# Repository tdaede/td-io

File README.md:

td-io is a JVS I/O board designed to adapt older JAMMA-compatible cabinets to the newer JVS standard, used by modern arcade hardware such as the Naomi and exA. It features a number of independent systems to translate signals, drive cabinet hardware, and power JVS games.

# Features at a glance

* Chainable JVS I/O implementing a 2L12B panel and coin inputs
* JVS to JAMMA video converter compatible with all monitors
* Mono/stereo audio amplifier for driving JAMMA speakers
* JVS power connector providing 3.3V via an on-board converter
* High reliability, low heat generation and all solid state caps
* Upgradeable firmware

# Comparison with other JVS I/O options

|               | TD-IO   | Capcom I/O   | Sega 838   | Exa I/O |
| ------------- | ------- | ------------ | ---------- | ------- |
| Lag (frames)  | 0       | 1            | 0          | 0       |
| Chaining      | ✔ | ❌ | ✔ | ✔ |
| Video         | ✔ | ✔ | ✔ | ❌ |
| Audio amp     | ✔ | ✔ | ❌ | ❌ |
| 3.3V power    | ✔ | ✔ | ❌ | ❌ |
| Amplified stereo | ✔ | ❌ | ❌ | ❌ |

# JVS inputs

The JVS I/O bus connects to the board via USB-style A and B connectors. Daisy chaining is supported. The I/O presents two players, each with a single joystick/lever and six buttons. Joystick and button 1-4 inputs are mapped to the JAMMA edge connector, and buttons 4-6 are mapped to a CPS2-style kick harness connector. Buttons are polled synchronously, ensuring microsecond-level latency.

Service, test, and tilt buttons are also supported. JAMMA's single service button is mapped to JVS player 1's service button.

The board also presents one or two coin slots, toggleable by a DIP switch. The board also features two coin meter drivers and two coin lockout drivers. Coins are locked out when the respective coin count is set to its max value (16383).

# Video

The board maps JVS-level video (0.7Vp-p, AC or DC coupled) to JAMMA levels (0-3V, DC coupled). This is achieved via a DC restore step using the sync signal, followed by a fixed amplification. The DC coupled output allows maximum compatibility with monitors such as the Nanao MS8 and capture devices such as the Splitfire which require it.

In addition, a sync combiner combines negative H/V sync to negative composite sync.

No rate conversion is performed - the monitor must support the same scan rates as the JVS game.

An EDID EEPROM is also attached to the VGA port, to identify as a 31kHz monitor.

# Audio

TD-IO provides a class-D audio amplifier, which can drive both mono and stereo speakers in JAMMA cabinets. For mono cabinets, audio is simply provided via the JAMMA edge. For stereo support, the cabinet's speakers should be connected to the JST NH header provided on the I/O. The pinout of this header is directly compatible with the Egret 2, and adapters can be easily made for other cabinets, such as the Aero.

The stereo/mono switch selects whether to mixdown the L/R channels to mono. It should be set to mono when using a mono cabinet via the JAMMA edge, and stereo when using a cabinet with the stereo header.

The stereo support is not directly compatible with nonstandard Neo Geo style stereo over JAMMA, with a common ground. For these cabinets, either use the TD-IO in mono mode, or rewire the cabinet to connect directly to the stereo header. The left/right negative speaker outputs should not be tied together.

## Aero City stereo adapter

| JST NH H4P-SHF-AA | Molex MLX 50-84-2042 |
| --- | --- |
| 1   | 2   |
| 2   | 3   |
| 3   | 1   |
| 4   | 4   |

# Power

An 8-pin JVS power connector forwards 12V and 5V from the cabinet to the JVS board. In addition, an on-board power supply generates 3.3V at up to 7A from the cabinet's 5V rail for systems that require it, such as Naomi.

The cabinet's 5V power supply must still be adequate to power the 3.3V converter.

The IO's electronics are protected from overvoltage and overcurrent by an automatically resetting protector.

# Firmware Updates

The board features an on-board RP2040 microcontroller, whose firmware can be updated over USB for feature enhancements or compatibility fixes.

To update the firmware, turn off power to the cabinet (if attached). Then, attach a USB cable to the micro USB connector. Hold down the white button on the RP2040 while plugging the USB connector into a PC. The TD-IO will then appear as a flash drive. Copy the firmware file (ending in .uf2) onto the drive. The TD-IO will then disconnect and be ready for use.

# Analog Input

The board features an unpopulated expansion header exposing 3 3.3V level analog inputs, designed for potentiometers for analog joystick or racing games. This feature is experimental and not yet implemented in the firmware.

# Where to buy

The board is not currently for sale, as testing is not yet complete.

# License

CERN-OHL-W

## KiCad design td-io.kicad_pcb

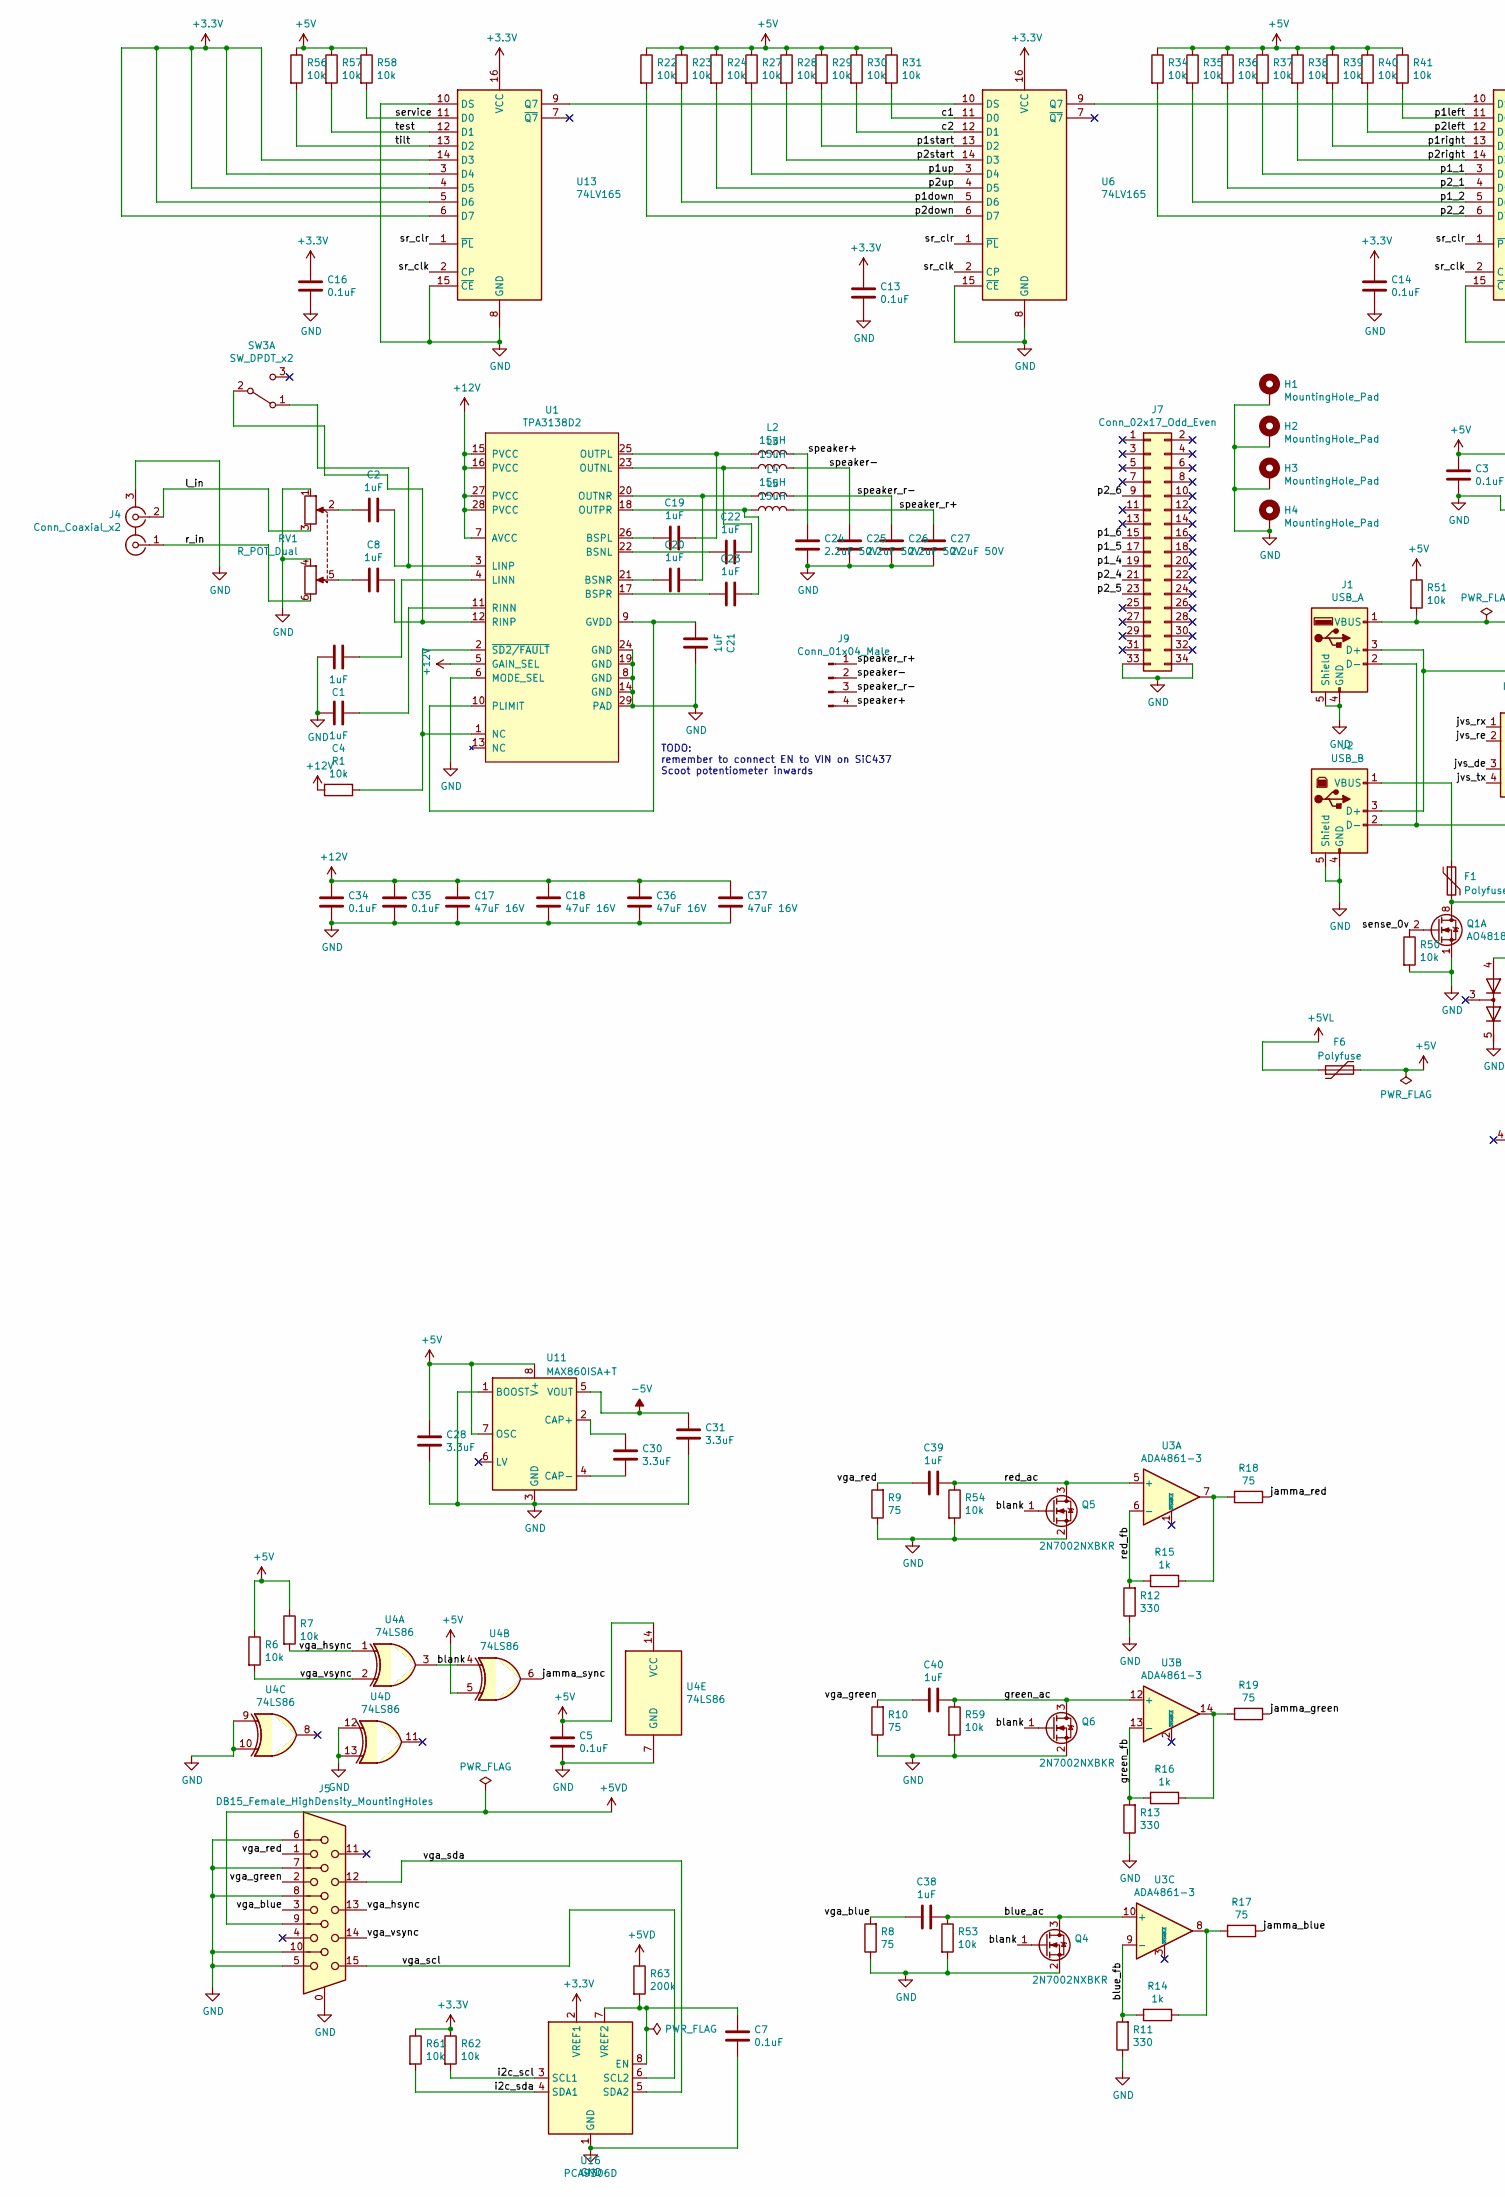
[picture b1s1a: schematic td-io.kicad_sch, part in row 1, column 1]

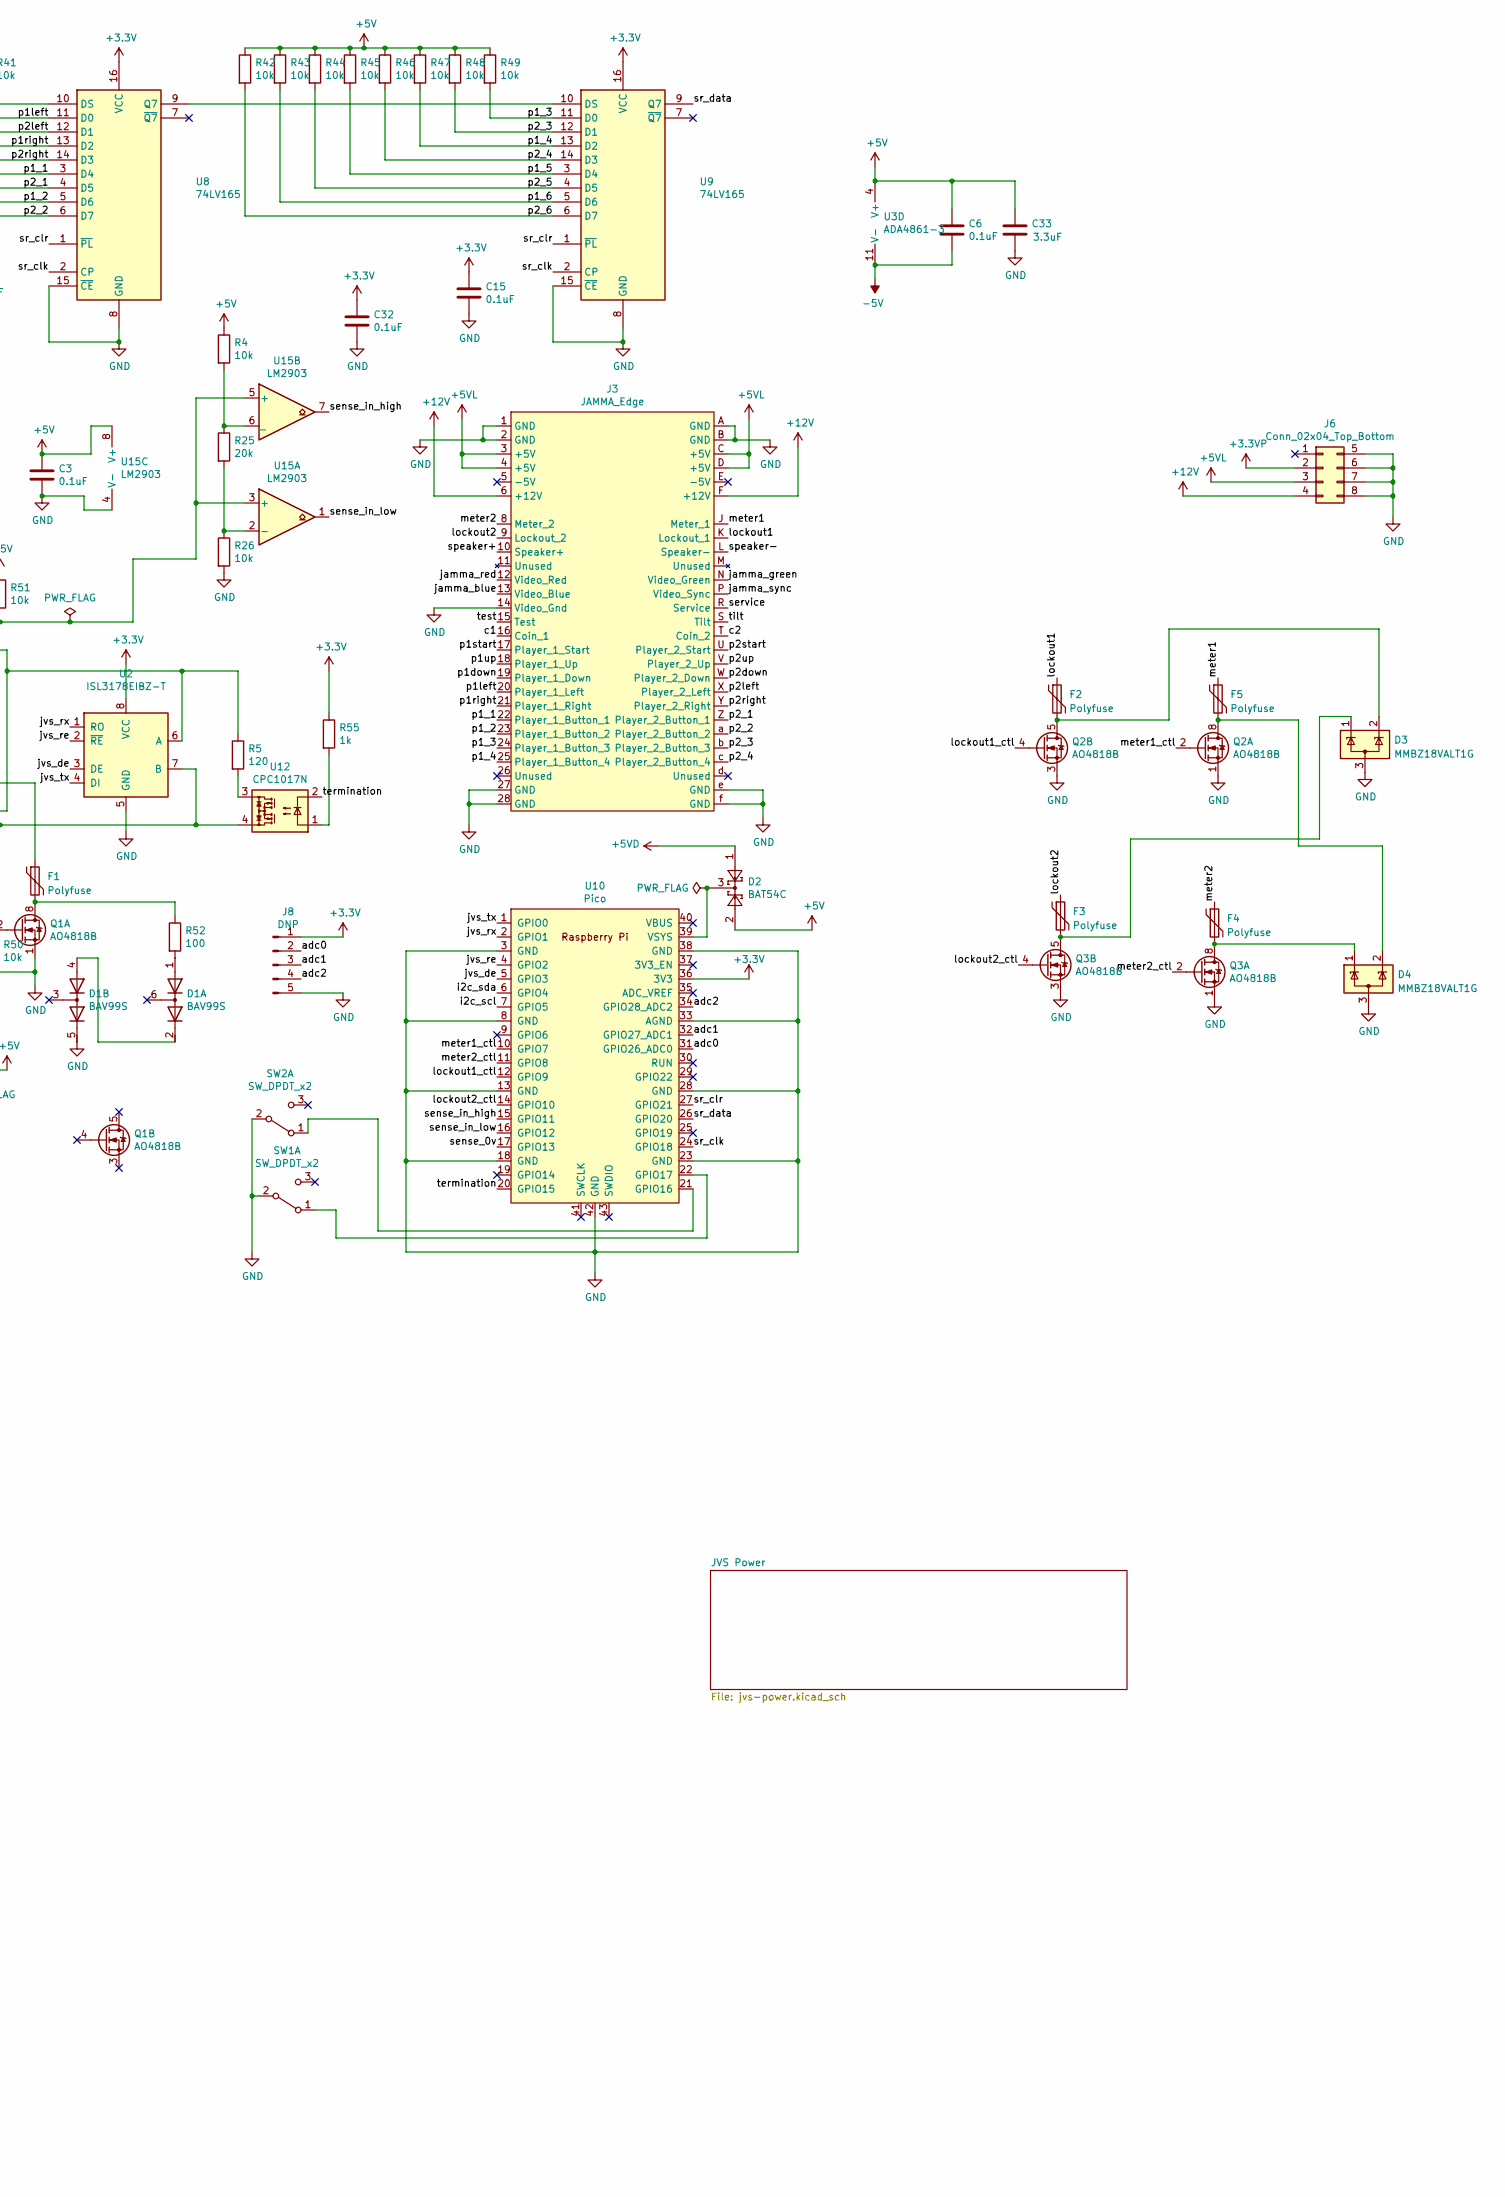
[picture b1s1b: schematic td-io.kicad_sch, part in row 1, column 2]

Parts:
C1, C2, C4, C8, C19, C20, C21, C22, C23, C38, C39, C40: 1uF; C_0805_2012Metric; Digikey 1276-2926-1-ND
C3, C5, C6, C7, C13, C14, C15, C16, C32, C34, C35: 0.1uF; C_0805_2012Metric; Digikey 1276-2444-1-ND
C17, C18, C36, C37: 47uF 16V; C_1210_3225Metric; Digikey 490-16309-1-ND
C24, C25, C26, C27: 2.2uF 50V; C_1210_3225Metric; Digikey 1276-2884-1-ND
C28, C30, C31, C33: 3.3uF; C_0805_2012Metric; Digikey 1276-6461-1-ND
D1: BAV99S; SOT-363_SC-70-6; Digikey 1727-4042-1-ND
D2: BAT54C; SOT-23; Digikey BAT54CFSCT-ND
D3, D4: MMBZ18VALT1G; SOT-23; Digikey MMBZ18VALT1GOSTR-ND
F1, F2, F3, F4, F5, F6: Polyfuse; R_1812_4532Metric; Digikey 507-1762-1-ND
H1, H2, H3, H4: MountingHole_Pad; MountingHole_3.2mm_M3_Pad_Via
J1: USB_A; USB_A_Molex_67643_Horizontal; Digikey SAM10870-ND
J2: USB_B; USB_B_OST_USB-B1HSxx_Horizontal; Digikey SAM10873-ND
J3: JAMMA_Edge; JAMMA
J4: Conn_Coaxial_x2; PJRAN2X1U01AUX; Digikey SC2534-ND
J5: DB15_Female_HighDensity_MountingHoles; DSUB-15-HD_Female_Horizontal_P2.29x2.5mm_EdgePinOffset8.35m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; Digikey Z13226-ND
J6: Conn_02x04_Top_Bottom; B08P-VL; Digikey 455-2365-ND
J7: Conn_02x17_Odd_Even; DF1BZ-34DP-2.5DS; Digikey H11039-ND
J8: DNP; PinHeader_1x05_P2.54mm_Vertical
J9: Conn_01x04_Male; JST_SH_B4B-NH-A_1x04_P2.50mm_Vertical; Digikey 455-4179-ND
L2, L3, L4, L5: 15uH; L_7.3x7.3_H4.5; Digikey 811-3582-1-ND
Q1, Q2, Q3: AO4818B; SOIC-8_3.9x4.9mm_P1.27mm; Digikey 785-1059-1-ND
Q4, Q5, Q6: 2N7002NXBKR; SOT-23; Digikey 1727-8642-1-ND
R1, R4, R6, R7, R22, R23, R24, R26, R27, R28, R29, R30, R31, R34, R35, R36, R37, R38, R39, R40, R41, R42, R43, R44, R45, R46, R47, R48, R49, R50, R51, R53, R54, R56, R57, R58, R59, R61, R62: 10k; R_0805_2012Metric; Digikey 311-10.0KCRCT-ND
R5: 120; R_0805_2012Metric; Digikey 13-RT0805FRE07120RLCT-ND
R8, R9, R10, R17, R18, R19: 75; R_0805_2012Metric; Digikey 311-75.0CRCT-ND
R11, R12, R13: 330; R_0805_2012Metric; Digikey 311-330CRCT-ND
R14, R15, R16, R55: 1k; R_0805_2012Metric; Digikey 311-1.00KCRCT-ND
R25: 20k; R_0805_2012Metric; Digikey 311-20.0KCRCT-ND
R52: 100; R_0805_2012Metric; Digikey 311-100CRCT-ND
R63: 200k; R_0805_2012Metric; Digikey 311-200KCRCT-ND
RV1: R_POT_Dual; PTV112-4420A-A503; Digikey PTV112-4420A-A503-ND
SW1, SW2, SW3: SW_DPDT_x2; SW_DPDT_CK_JS202011JCQN; Digikey CKN10723CT-ND
U1: TPA3138D2; HTSSOP-28-1EP_4.4x9.7mm_P0.65mm_tpa3138_ThermalVias; Digikey 296-50219-ND
U2: ISL3178EIBZ-T; SOIC-8_3.9x4.9mm_P1.27mm; Digikey 20-ISL3178EIBZ-TCT-ND
U3: ADA4861-3; SOIC-14_3.9x8.7mm_P1.27mm; Digikey ADA4861-3YRZ-RL7CT-ND
U4: 74LS86; SOIC-14_3.9x8.7mm_P1.27mm; Digikey 296-8201-1-ND
U6, U8, U9, U13: 74LV165; SOIC-16_3.9x9.9mm_P1.27mm; Digikey 296-SN74LV165ADRG3CT-ND
U10: Pico; RPi_Pico_SMD; Digikey 2648-SC0915CT-ND
U11: MAX860ISA+T; SOIC-8_3.9x4.9mm_P1.27mm; Digikey MAX860ISA+TCT-ND
U12: CPC1017N; SOP-4_3.8x4.1mm_P2.54mm; Digikey CLA153-ND
U15: LM2903; SOIC-8_3.9x4.9mm_P1.27mm; Digikey 296-27463-1-ND
U16: PCA9306D; SO-8_3.9x4.9mm_P1.27mm; Digikey 568-4215-1-ND

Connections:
+3.3V: C13.1, C14.1, C15.1, C16.1, C32.1, J8.1, R55.1, R61.1, R62.1, U2.8 (VCC), U6.16 (VCC), U8.16 (VCC), U9.16 (VCC), U10.36 (3V3), U13.3 (D4), U13.4 (D5), U13.5 (D6), U13.6 (D7), U13.14 (D3), U13.16 (VCC), U16.2 (VREF1)
+3.3VP: J6.2; also elsewhere on the board
+5V: C3.1, C5.1, C6.1, C28.1, C33.1, D2.2, F6.2, R4.1, R6.1, R7.1, R22.1, R23.1, R24.1, R27.1, R28.1, R29.1, R30.1, R31.1, R34.1, R35.1, R36.1, R37.1, R38.1, R39.1, R40.1, R41.1, R42.1, R43.1, R44.1, R45.1, R46.1, R47.1, R48.1, R49.1, R51.1, R56.1, R57.1, R58.1, U3.4 (V+), U4.5, U4.14 (VCC), U11.7 (OSC), U11.8 (V+), U15.8 (V+)
+5VD: D2.1, J5.9, R63.1
+5VL: F6.1, J3.3 (+5V), J3.4 (+5V), J3.C (+5V), J3.D (+5V), J6.3; also elsewhere on the board
+12V: C17.1, C18.1, C34.1, C35.1, C36.1, C37.1, J3.6 (+12V), J3.F (+12V), J6.4, R1.2, U1.5 (GAIN_SEL), U1.7 (AVCC), U1.15 (PVCC), U1.16 (PVCC), U1.27 (PVCC), U1.28 (PVCC)
-5V: C6.2, C31.1, U3.11 (V-), U11.5 (VOUT)
/adc0: J8.2, U10.31 (GPIO26_ADC0)
/adc1: J8.3, U10.32 (GPIO27_ADC1)
/adc2: J8.4, U10.34 (GPIO28_ADC2)
/blank: Q4.1 (G), Q5.1 (G), Q6.1 (G), U4.3, U4.4
/blue_ac: C38.1, Q4.3 (D), R53.1, U3.10 (+)
/blue_fb: R11.2, R14.2, U3.9 (-)
/c1: J3.16 (Coin_1), R31.2, U6.11 (D0)
/c2: J3.T (Coin_2), R30.2, U6.12 (D1)
/green_ac: C40.1, Q6.3 (D), R59.1, U3.12 (+)
/green_fb: R13.2, R16.2, U3.13 (-)
/i2c_scl: R62.2, U10.7 (GPIO5), U16.3 (SCL1)
/i2c_sda: R61.2, U10.6 (GPIO4), U16.4 (SDA1)
/jamma_blue: J3.13 (Video_Blue), R17.1
/jamma_green: J3.N (Video_Green), R19.1
/jamma_red: J3.12 (Video_Red), R18.1
/jamma_sync: J3.P (Video_Sync), U4.6
/jvs_de: U2.3 (DE), U10.5 (GPIO3)
/jvs_re: U2.2 (~RE), U10.4 (GPIO2)
/jvs_rx: U2.1 (RO), U10.2 (GPIO1)
/jvs_tx: U2.4 (DI), U10.1 (GPIO0)
/l_in: J4.2 (IN2), RV1.3
/lockout1: F2.1, J3.K (Lockout_1)
/lockout1_ctl: Q2.4 (G2), U10.12 (GPIO9)
/lockout2: F3.1, J3.9 (Lockout_2)
/lockout2_ctl: Q3.4 (G2), U10.14 (GPIO10)
/meter1: F5.1, J3.J (Meter_1)
/meter1_ctl: Q2.2 (G1), U10.10 (GPIO7)
/meter2: F4.1, J3.8 (Meter_2)
/meter2_ctl: Q3.2 (G1), U10.11 (GPIO8)
/p1_1: J3.22 (Player_1_Button_1), R37.2, U8.3 (D4)
/p1_2: J3.23 (Player_1_Button_2), R35.2, U8.5 (D6)
/p1_3: J3.24 (Player_1_Button_3), R49.2, U9.11 (D0)
/p1_4: J3.25 (Player_1_Button_4), J7.19, R47.2, U9.13 (D2)
/p1_5: J7.17, R45.2, U9.3 (D4)
/p1_6: J7.15, R43.2, U9.5 (D6)
/p1down: J3.19 (Player_1_Down), R23.2, U6.5 (D6)
/p1left: J3.20 (Player_1_Left), R41.2, U8.11 (D0)
/p1right: J3.21 (Player_1_Right), R39.2, U8.13 (D2)
/p1start: J3.17 (Player_1_Start), R29.2, U6.13 (D2)
/p1up: J3.18 (Player_1_Up), R27.2, U6.3 (D4)
/p2_1: J3.Z (Player_2_Button_1), R36.2, U8.4 (D5)
/p2_2: J3.a (Player_2_Button_2), R34.2, U8.6 (D7)
/p2_3: J3.b (Player_2_Button_3), R48.2, U9.12 (D1)
/p2_4: J3.c (Player_2_Button_4), J7.21, R46.2, U9.14 (D3)
/p2_5: J7.23, R44.2, U9.4 (D5)
/p2_6: J7.9, R42.2, U9.6 (D7)
/p2down: J3.W (Player_2_Down), R22.2, U6.6 (D7)
/p2left: J3.X (Player_2_Left), R40.2, U8.12 (D1)
/p2right: J3.Y (Player_2_Right), R38.2, U8.14 (D3)
/p2start: J3.U (Player_2_Start), R28.2, U6.14 (D3)
/p2up: J3.V (Player_2_Up), R24.2, U6.4 (D5)
/r_in: J4.1 (IN1), RV1.6
/red_ac: C39.1, Q5.3 (D), R54.1, U3.5 (+)
/red_fb: R12.2, R15.2, U3.6 (-)
/sense_0v: Q1.2 (G1), R50.1, U10.17 (GPIO13)
/sense_in_high: U10.15 (GPIO11), U15.7
/sense_in_low: U10.16 (GPIO12), U15.1
/service: J3.R (Service), R58.2, U13.11 (D0)
/speaker+: C24.1, J3.10 (Speaker+), J9.4, L2.2
/speaker-: C25.1, J3.L (Speaker-), J9.2, L3.2
/speaker_r+: C27.1, J9.1, L5.2
/speaker_r-: C26.1, J9.3, L4.2
/sr_clk: U6.2 (CP), U8.2 (CP), U9.2 (CP), U10.24 (GPIO18), U13.2 (CP)
/sr_clr: U6.1 (~PL), U8.1 (~PL), U9.1 (~PL), U10.27 (GPIO21), U13.1 (~PL)
/sr_data: U9.9 (Q7), U10.26 (GPIO20)
/termination: U10.20 (GPIO15), U12.2
/test: J3.15 (Test), R57.2, U13.12 (D1)
/tilt: J3.S (Tilt), R56.2, U13.13 (D2)
/vga_blue: C38.2, J5.3, R8.2
/vga_green: C40.2, J5.2, R10.2
/vga_hsync: J5.13, R7.2, U4.1
/vga_red: C39.2, J5.1, R9.2
/vga_scl: J5.15, U16.6 (SCL2)
/vga_sda: J5.12, U16.5 (SDA2)
/vga_vsync: J5.14, R6.2, U4.2
GND: C1.1, C3.2, C4.1, C5.2, C7.2, C13.2, C14.2, C15.2, C16.2, C17.2, C18.2, C21.1, C24.2, C25.2, C26.2, C27.2, C28.2, C31.2, C32.2, C33.2, C34.2, C35.2, C36.2, C37.2, D1.5 (K4), D3.3 (A), D4.3 (A), H1.1, H2.1, H3.1, H4.1, J1.4 (GND), J1.5 (Shield), J2.4 (GND), J2.5 (Shield), J3.1 (GND), J3.2 (GND), J3.14 (Video_Gnd), J3.27 (GND), J3.28 (GND), J3.A (GND), J3.B (GND), J3.e (GND), J3.f (GND), J4.3 (EXT), J5.0, J5.5, J5.6, J5.7, J5.8, J5.10, J6.5, J6.6, J6.7, J6.8, J7.33, J7.34, J8.5, Q1.1 (S1), Q2.1 (S1), Q2.3 (S2), Q3.1 (S1), Q3.3 (S2), Q4.2 (S), Q5.2 (S), Q6.2 (S), R8.1, R9.1, R10.1, R11.1, R12.1, R13.1, R26.2, R50.2, R53.2, R54.2, R59.2, RV1.1, RV1.4, SW1.2 (B), SW2.2 (B), U1.6 (MODE_SEL), U1.8 (GND), U1.14 (GND), U1.19 (GND), U1.24 (GND), U1.29 (PAD), U2.5 (GND), U4.7 (GND), U4.9, U4.10, U4.12, U4.13, U6.8 (GND), U6.15 (~CE), U8.8 (GND), U8.15 (~CE), U9.8 (GND), U9.15 (~CE), U10.3 (GND), U10.8 (GND), U10.13 (GND), U10.18 (GND), U10.23 (GND), U10.28 (GND), U10.33 (AGND), U10.38 (GND), U10.42 (GND), U11.1 (BOOST), U11.3 (GND), U13.8 (GND), U13.10 (DS), U13.15 (~CE), U15.4 (V-), U16.1 (GND); also elsewhere on the board
unnamed: C1.2, U1.4 (LINN)
unnamed: C2.1, SW3.1 (A), U1.3 (LINP)
unnamed: C2.2, RV1.2
unnamed: C4.2, U1.11 (RINN)
unnamed: C7.1, R63.2, U16.7 (VREF2), U16.8 (EN)
unnamed: C8.1, SW3.2 (B), U1.12 (RINP)
unnamed: C8.2, RV1.5
unnamed: C19.1, L2.1, U1.25 (OUTPL)
unnamed: C19.2, U1.26 (BSPL)
unnamed: C20.1, L4.1, U1.20 (OUTNR)
unnamed: C20.2, U1.21 (BSNR)
unnamed: C21.2, U1.9 (GVDD), U1.10 (PLIMIT)
unnamed: C22.1, L3.1, U1.23 (OUTNL)
unnamed: C22.2, U1.22 (BSNL)
unnamed: C23.1, L5.1, U1.18 (OUTPR)
unnamed: C23.2, U1.17 (BSPR)
unnamed: C30.1, U11.2 (CAP+)
unnamed: C30.2, U11.4 (CAP-)
unnamed: D1.1 (A1), R52.2
unnamed: D1.2 (K2), D1.4 (A3)
unnamed: D2.3, U10.39 (VSYS)
unnamed: D3.1 (K), F3.2, Q3.5 (D2), Q3.6 (D2)
unnamed: D3.2 (K), F2.2, Q2.5 (D2), Q2.6 (D2)
unnamed: D4.1 (K), F4.2, Q3.7 (D1), Q3.8 (D1)
unnamed: D4.2 (K), F5.2, Q2.7 (D1), Q2.8 (D1)
unnamed: F1.1, J2.1 (VBUS)
unnamed: F1.2, Q1.7 (D1), Q1.8 (D1), R52.1
unnamed: J1.1 (VBUS), R51.2, U15.3 (+), U15.5 (+)
unnamed: J1.2 (D-), J2.2 (D-), U2.7 (B), U12.4
unnamed: J1.3 (D+), J2.3 (D+), R5.1, U2.6 (A)
unnamed: R1.1, U1.1 (NC), U1.2 (~SD2/FAULT)
unnamed: R5.2, U12.3
unnamed: R14.1, R17.2, U3.8
unnamed: R15.1, R18.2, U3.7
unnamed: R16.1, R19.2, U3.14
unnamed: R4.2, R25.1, U15.6 (_)
unnamed: R25.2, R26.1, U15.2 (-)
unnamed: R55.2, U12.1
unnamed: SW1.1 (A), U10.22 (GPIO17)
unnamed: SW2.1 (A), U10.21 (GPIO16)
unnamed: U6.9 (Q7), U8.10 (DS)
unnamed: U8.9 (Q7), U9.10 (DS)
unnamed: U6.10 (DS), U13.9 (Q7)

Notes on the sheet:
TODO: remember to connect EN to VIN on SiC437 Scoot potentiometer inwards

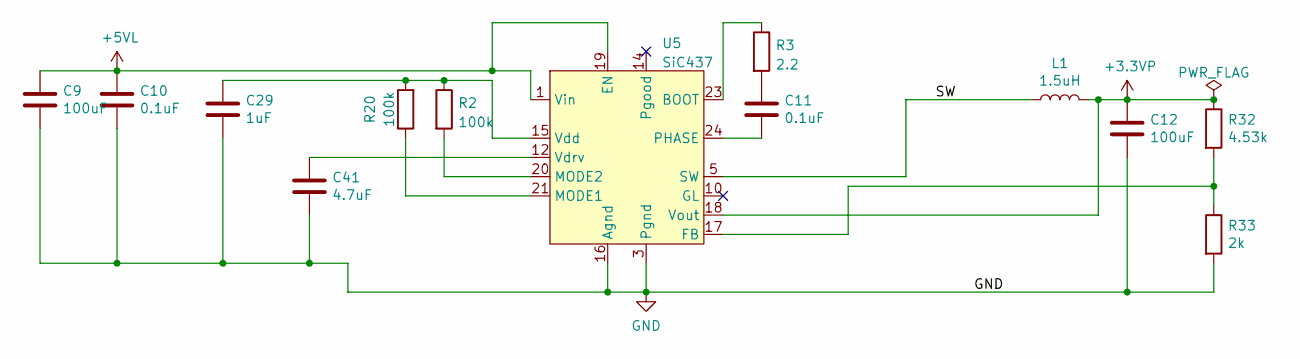
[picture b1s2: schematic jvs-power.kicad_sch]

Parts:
C9, C12: 100uF; C_1210_3225Metric; Digikey 1276-1092-1-ND
C10, C11: 0.1uF; C_0805_2012Metric; Digikey 1276-2444-1-ND
C29: 1uF; C_0805_2012Metric; Digikey 311-1365-1-ND
C41: 4.7uF; C_0805_2012Metric; Digikey 1276-1259-1-ND
L1: 1.5uH; L_Bourns_SRP7028A_7.3x6.6mm; Digikey SRP7050TA-1R5MCT-ND
R2, R20: 100k; R_0805_2012Metric; Digikey 311-100KCRCT-ND
R3: 2.2; R_0805_2012Metric; Digikey 311-2.2ARCT-ND
R32: 4.53k; R_0805_2012Metric
R33: 2k; R_0805_2012Metric
U5: SiC437; Vishay_PowerPAK_MLP44-24L; Digikey SIC437AED-T1-GE3CT-ND

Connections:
+3.3VP: C12.1, L1.2, R32.1, U5.18 (Vout); also elsewhere on the board
+5VL: C9.1, C10.1, U5.1 (Vin), U5.2 (Vin), U5.19 (EN), U5.22 (Vin), U5.26 (Vin); also elsewhere on the board
/JVS Power/SW: L1.1, U5.5 (SW), U5.6 (SW), U5.7 (SW), U5.8 (SW), U5.9 (SW)
GND: C9.2, C10.2, C12.2, C29.2, C41.2, R33.2, U5.3 (Pgnd), U5.4 (Pgnd), U5.13 (Pgnd), U5.16 (Agnd), U5.25 (Agnd), U5.27 (Pgnd); also elsewhere on the board
unnamed: C11.1, R3.2
unnamed: C11.2, U5.24 (PHASE)
unnamed: C29.1, R2.1, R20.2, U5.15 (Vdd)
unnamed: C41.1, U5.12 (Vdrv)
unnamed: R2.2, U5.20 (MODE2)
unnamed: R3.1, U5.23 (BOOT)
unnamed: R20.1, U5.21 (MODE1)
unnamed: R32.2, R33.1, U5.17 (FB)

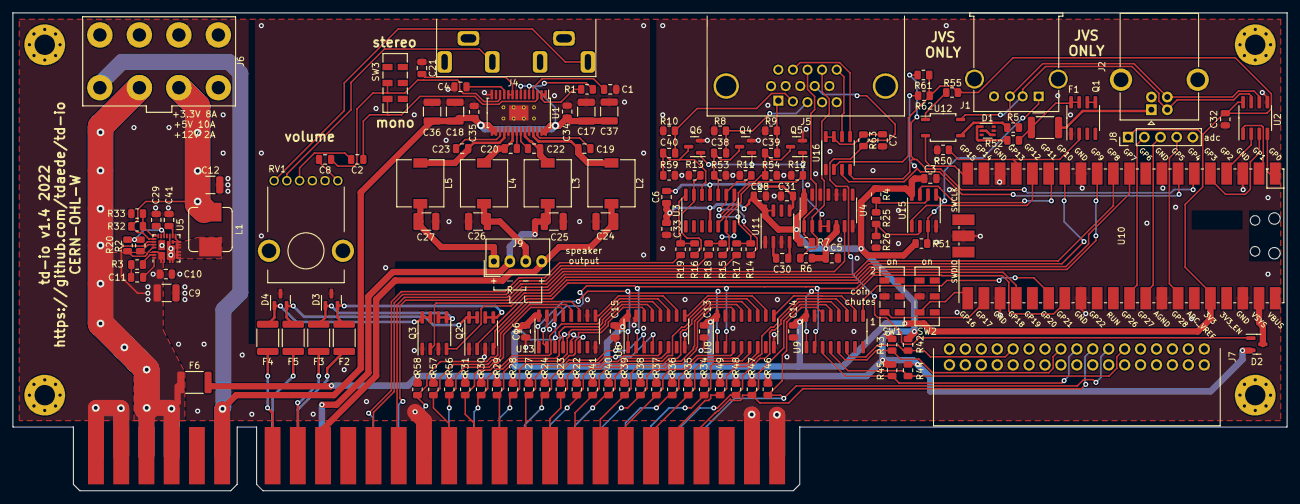
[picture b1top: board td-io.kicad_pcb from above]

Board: 2 copper layers, 200.0 x 75.0 mm, 154 parts (0 on the bottom side), 135 nets.

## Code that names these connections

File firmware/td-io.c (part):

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#include "edid.h"
#include <string.h>

const uint PIN_JVS_RE = 2;
const uint PIN_JVS_DE = 3;

const uint PIN_JVS_SENSE_2_5V = 14;
const uint PIN_JVS_SENSE_0V = 13;
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const uint PIN_JVS_SENSE_IN_HIGH = 11;
const uint PIN_JVS_SENSE_IN_LOW = 12;

const uint PIN_SR_DATA = 20;
const uint PIN_SR_CLK = 18;
const uint PIN_SR_SH = 21;

const uint PIN_METER1 = 7;
const uint PIN_METER2 = 8;
const uint PIN_LOCKOUT1 = 10;
const uint PIN_LOCKOUT2 = 9;

const uint PIN_LED_ENUMERATED = PICO_DEFAULT_LED_PIN;
const uint PIN_DIP1 = 17;
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}

void start_transmit() {
    gpio_put(PIN_JVS_RE, 1); // disable receive
    if (jvs_comm_method == 0) {
        // un-upgraded jvs needs at least 100us here
        busy_wait_us_32(200);    // 200us min for exa compat
    }
    gpio_put(PIN_JVS_DE, 1); // enable transmitter
}

void stop_transmit() {
    uart_tx_wait_blocking(uart0);
    gpio_put(PIN_JVS_DE, 0); // disable transmitter
    gpio_put(PIN_JVS_RE, 0); // enable receiver
}

void send_message(uint8_t status, uint8_t* m, uint8_t msg_len) {
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    gpio_put(PIN_SR_SH, 1);
    for (int i = 0; i < 32; i++) {
        r >>= 1;
        r |= (gpio_get(PIN_SR_DATA) ? 1 : 0) << 31;
        gpio_put(PIN_SR_CLK, 1);
        gpio_put(PIN_SR_CLK, 0);
    }
    gpio_put(PIN_SR_SH, 0);
    return ~r;
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    prev_coin_p2 = switches >> SR_C2 & 1;

    if (meter_timeout_p1) meter_timeout_p1--;
    gpio_put(PIN_METER1, meter_timeout_p1 > 0);

    if (meter_timeout_p2) meter_timeout_p2--;
    gpio_put(PIN_METER2, meter_timeout_p2 > 0);

    gpio_put(PIN_LOCKOUT1, coin_count_p1 >= 16383);
    gpio_put(PIN_LOCKOUT2, coin_count_p2 >= 16383);
}

int main() {
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    uart_set_translate_crlf(uart0, false);
    gpio_set_function(0, GPIO_FUNC_UART);
    gpio_set_function(1, GPIO_FUNC_UART);
    gpio_init(PIN_JVS_RE);
    gpio_put(PIN_JVS_RE, 0); // enable receiver
    gpio_set_dir(PIN_JVS_RE, GPIO_OUT);
    gpio_init(PIN_JVS_DE);
    gpio_put(PIN_JVS_DE, 0); //disable transmitter
    gpio_set_dir(PIN_JVS_DE, GPIO_OUT);
    gpio_init(PIN_JVS_SENSE_2_5V);
    gpio_put(PIN_JVS_SENSE_2_5V, 1); // always appear present
    gpio_set_dir(PIN_JVS_SENSE_2_5V, GPIO_OUT);
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    gpio_put(PIN_JVS_SENSE_0V, 0);
    gpio_set_dir(PIN_JVS_SENSE_0V, GPIO_OUT);
    gpio_init(PIN_JVS_TERMINATION);
    gpio_put(PIN_JVS_TERMINATION, 1); // disable termination by default
    gpio_set_dir(PIN_JVS_TERMINATION, GPIO_OUT);
    gpio_init(PIN_JVS_SENSE_IN_LOW);
    gpio_set_dir(PIN_JVS_SENSE_IN_LOW, GPIO_IN);
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    gpio_pull_up(PIN_JVS_SENSE_IN_HIGH);

    // sr
    gpio_init(PIN_SR_DATA);
    gpio_set_dir(PIN_SR_DATA, GPIO_IN);
    gpio_init(PIN_SR_CLK);
    gpio_put(PIN_SR_CLK, 0);
    gpio_set_dir(PIN_SR_CLK, GPIO_OUT);
    gpio_init(PIN_SR_SH);
    gpio_put(PIN_SR_SH, 0);
    gpio_set_dir(PIN_SR_SH, GPIO_OUT);

    // coin/lockout drivers
    gpio_init(PIN_METER1);
    gpio_put(PIN_METER1, 0);
    gpio_set_dir(PIN_METER1, GPIO_OUT);
    gpio_init(PIN_METER2);
    gpio_put(PIN_METER2, 0);
    gpio_set_dir(PIN_METER2, GPIO_OUT);
    gpio_init(PIN_LOCKOUT1);
    gpio_put(PIN_LOCKOUT1, 0);
    gpio_set_dir(PIN_LOCKOUT1, GPIO_OUT);
    gpio_init(PIN_LOCKOUT2);
    gpio_put(PIN_LOCKOUT2, 0);
    gpio_set_dir(PIN_LOCKOUT2, GPIO_OUT);

    // ui
    gpio_init(PIN_LED_ENUMERATED);
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
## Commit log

2021-02-02 Update schematic
2021-02-02 Swap male to female VGA connector
2021-02-04 Swap audio jacks out
2021-02-06 Add alternative power supply
2021-02-07 Add JVS chaining support
2021-02-08 More layout fixes
2021-02-08 Switch from 74lv166 to 74lv165
2021-02-08 Add service/test/tilt
2021-02-08 Swap to ADA4891-3.
2021-02-08 Switch to class D amp
2021-02-10 more layout
2021-02-16 More PCB layout
2021-02-16 update pcb
2021-02-16 move stuff around a bit more
2021-02-17 minor production changes
2021-02-26 BOM updates
2021-02-28 Add todo
2021-03-02 Add more todos
2021-03-02 Add initial firmware
2021-03-03 implement button mapping
2021-03-03 fix shift register order
2021-03-04 Add chaining support
2021-03-04 fix meter pin mappings
2021-03-09 Support 0x15 message.
2021-03-10 Add pico_sdk_import.cmake.
2021-03-28 new footprints
2021-03-29 change switch
2021-03-29 Add readme
2021-03-29 Move some tracks around
2021-03-29 too much mediawiki
2021-03-29 add note about latency
2021-04-04 Add LED for enumeration status
2021-04-04 Add dip switch to toggle between 1 and 2 coin slots
2021-04-04 add dc restoration and incrase schematic size
2021-04-12 more fixes
2021-04-21 final edits
2021-04-21 Add delay
2021-05-04 Add JVS chaining support.
    Also fix DIP assignments.
2021-05-04 add todos
2021-05-09 ws2812
2021-05-18 BOM changes
2021-05-27 Change check boxes to be green in Github
2021-05-27 Add amplified stereo line
2021-05-27 Fix bullet list grammar
2021-05-27 Add photo
2021-05-27 add photo to readme
2021-05-27 Add Aero City adapter pinout
2021-05-27 Correct capcom chaining information
2021-09-23 Poll for coins even while no active jvs polling is occurring every 20ms. JVS coin processing rate limited to 12ms.
2021-12-05 changes for 1.2
2021-12-05 thermal opt
2021-12-07 repour
2022-03-08 Update to KiCAD 6.0 and make some parts availability edits
2022-03-08 drop i2c rom
2022-03-08 convert pcb to kicad 6
2022-03-08 some pcb layout action
2022-03-10 finish layout
2022-03-11 update PCB footprints from libraries
2022-03-11 update to new psu
2022-03-11 small fixes
2022-03-11 Use Apache 2.0 license for firmware.
2022-03-11 switch pca9306 to soic-8 footprint
2022-03-12 add 3d models
2022-03-12 add changelog
2022-03-20 re test zones
2022-07-23 Fix TILT magic number + typo
2022-07-24 Implementation of the 0x20 extended JVS protocol (COMMCHG and COMMSUP)
2022-09-10 Limit service from being processed more often than coins. JVS' + noisy switches can cause coin problems.
2022-09-16 forking it hard
2022-09-17 Update td-io.c
    Disable reading buttons the old way, hook up test button directly to gpio22
2022-09-17 Simplify code by ripping out stuff I dont need and freeing up some pins
2022-09-17 empty placeholders for new pins
2022-09-17 allocate pins for buttons
2022-09-17 Read inputs into bitflags
2022-09-17 Doc + id changes
2022-09-17 Simplify sense and termination, since daisy chaining is not supported
2022-09-18 Updated pcb with onboard pico
2022-09-18 Move some pins
2022-09-18 Add some breakout pins
2022-09-18 Clean up pcb
2022-09-18 Removed stuff I don't need
2022-09-18 Make Readme reflect this device, not td-io
2022-11-30 Implement coin meter timeout (min/max pulse length). Fix meter pinout.
2023-02-07 Add edid emulation support.
    Uses third party pico_i2c_slave library.
2023-02-07 Update feature matrix to reflect new Exa-IO version.
2023-02-24 add missing edid.h file
2023-05-08 Add acceptance test
2023-05-08 Move acceptance test to docs folder
2023-05-08 Fix test numbering
2023-08-01 Implement 0x2F (re-transmit) command.
2023-09-08 Implement (dummy) analog read command
2023-10-10 Use normal JVS turnaround delay when on default comm speed.
2023-10-10 bump firmware version
2025-05-20 Add missing schematic sheet
